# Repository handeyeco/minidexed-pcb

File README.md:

> [!CAUTION]
> This project was made by a JavaScript developer, not an electrical engineer.
>
> It should be assumed that everything is wrong and the project will set your house on fire.
>
> I am not responsible for anything ever.

# MiniDexed PCB

Custom PCB for [MiniDexed](https://github.com/probonopd/MiniDexed), an open-source FM synthesizer. It has:

- An endless encoder
- 3 Cherry buttons (back/home/select)
- A 1602 display
- 3.5mm TRS MIDI in/thru/out
- USB MIDI
- 3.5mm TRS audio out (via the PCM5102 DAC)

See the [writeup on my blog](https://handeyeco.github.io/tech-blog/minidexed-pcb/) for a full explanation of the circuit.

Thanks to lots of folks!

- [probonopd](https://github.com/probonopd) and the whole MiniDexed team
- [diyelectromusic](https://diyelectromusic.com/) for MiniDexed work and PCB design notes
- The whole [Dexed](https://github.com/asb2m10/dexed) lineage
- The [KiCad](https://www.kicad.org/) maintainers

## Builds

Look in `/gerbers/` for build files and BOMs.

### 20240727

Working with the [MiniDexed 2024-01-16 release](https://github.com/probonopd/MiniDexed/releases/tag/2024-01-16).

No known issues (although MIDI out is untested right now). The whole thing is about the size of a Korg NTS-1 and costs roughly $15/PCB to make (including SMT assembly and SMT parts; not including the Pi, THT components, or shipping).

Required changes to `minidexed.ini`:

```
# Sound device
SoundDevice=i2s
#SoundDevice=pwm
#SoundDevice=hdmi

# ...unchanged...

ButtonPinBack=16
ButtonActionBack=click
ButtonPinSelect=27
ButtonActionSelect=click
ButtonPinHome=26
ButtonActionHome=click

# ...unchanged...
```

- For JLCPCB PCB assembly
  - SMD BOM is `minidexed-bom-smd.csv`
  - Pick-and-place position file is `minidexed-bottom-pos.csv`
  - I'm not an expert and can't help much, I followed [this video](https://www.youtube.com/watch?v=VejO8rDdhzo)
- Non-SMD components:
  - x1 [RPi](https://www.adafruit.com/product/3055)
    - I used the 3 because the 4 is hot AF
  - x3 [Cherry switches](https://www.digikey.com/en/products/detail/cherry-americas-llc/MX1A-E1NW/20180) 
    - PCB-mount is best: `MX1A-_1NW`, the `W` is PCB mount
  - x3 Cherry compatible key caps
  - x1 Encoder
    - I have no idea what encoder I used, [maybe this](https://www.digikey.com/en/products/detail/bourns-inc/PEC11R-4215F-S0012/4499664?s=N4IgTCBcDaIGwFYwFoAKBRAwgRmwJWQBYxsEAxZAZWwgF0BfIA)
    - I used a switched encoder
    - Shaft height/style depends on the enclosure/knob
  - x1 Knob for the encoder
  - x4 3.5mm TRS
    - [Like this one](https://www.mouser.com/ProductDetail/SparkFun/PRT-08032?qs=WyAARYrbSnZFBWwuc8Qktw%3D%3D)
    - I like the switched ones because they have 5 pins vs 3 pins which makes the connection to the PCB more solid
    - MIDI is TRS, that's why there's 4 (x3 MIDI, x1 audio)
  - x1 16x2 LCD display
    - My understanding is that these 16x2 LCDs are pretty generic, something [like this](https://www.adafruit.com/product/181) should work
  - x1 10k (103) trim pot
    - For the LCD; [like these](https://www.amazon.com/gp/product/B0CZVY726N)
  - x1 2x20 2.54mm female header (for the Pi)
  - x1 1x16 2.54mm male header (for the LCD)
  - x1 1x16 2.54mm female header (for the LCD)
    - optional, I soldered mine into the PCB to keep things short
  - I think all the mounting holes and spacers are M2.5 (since that's what the Pi uses)
  - All this stuff is pretty generic and highly available
  - **Don't trust me**, double check your footprints or be prepared to reorder things

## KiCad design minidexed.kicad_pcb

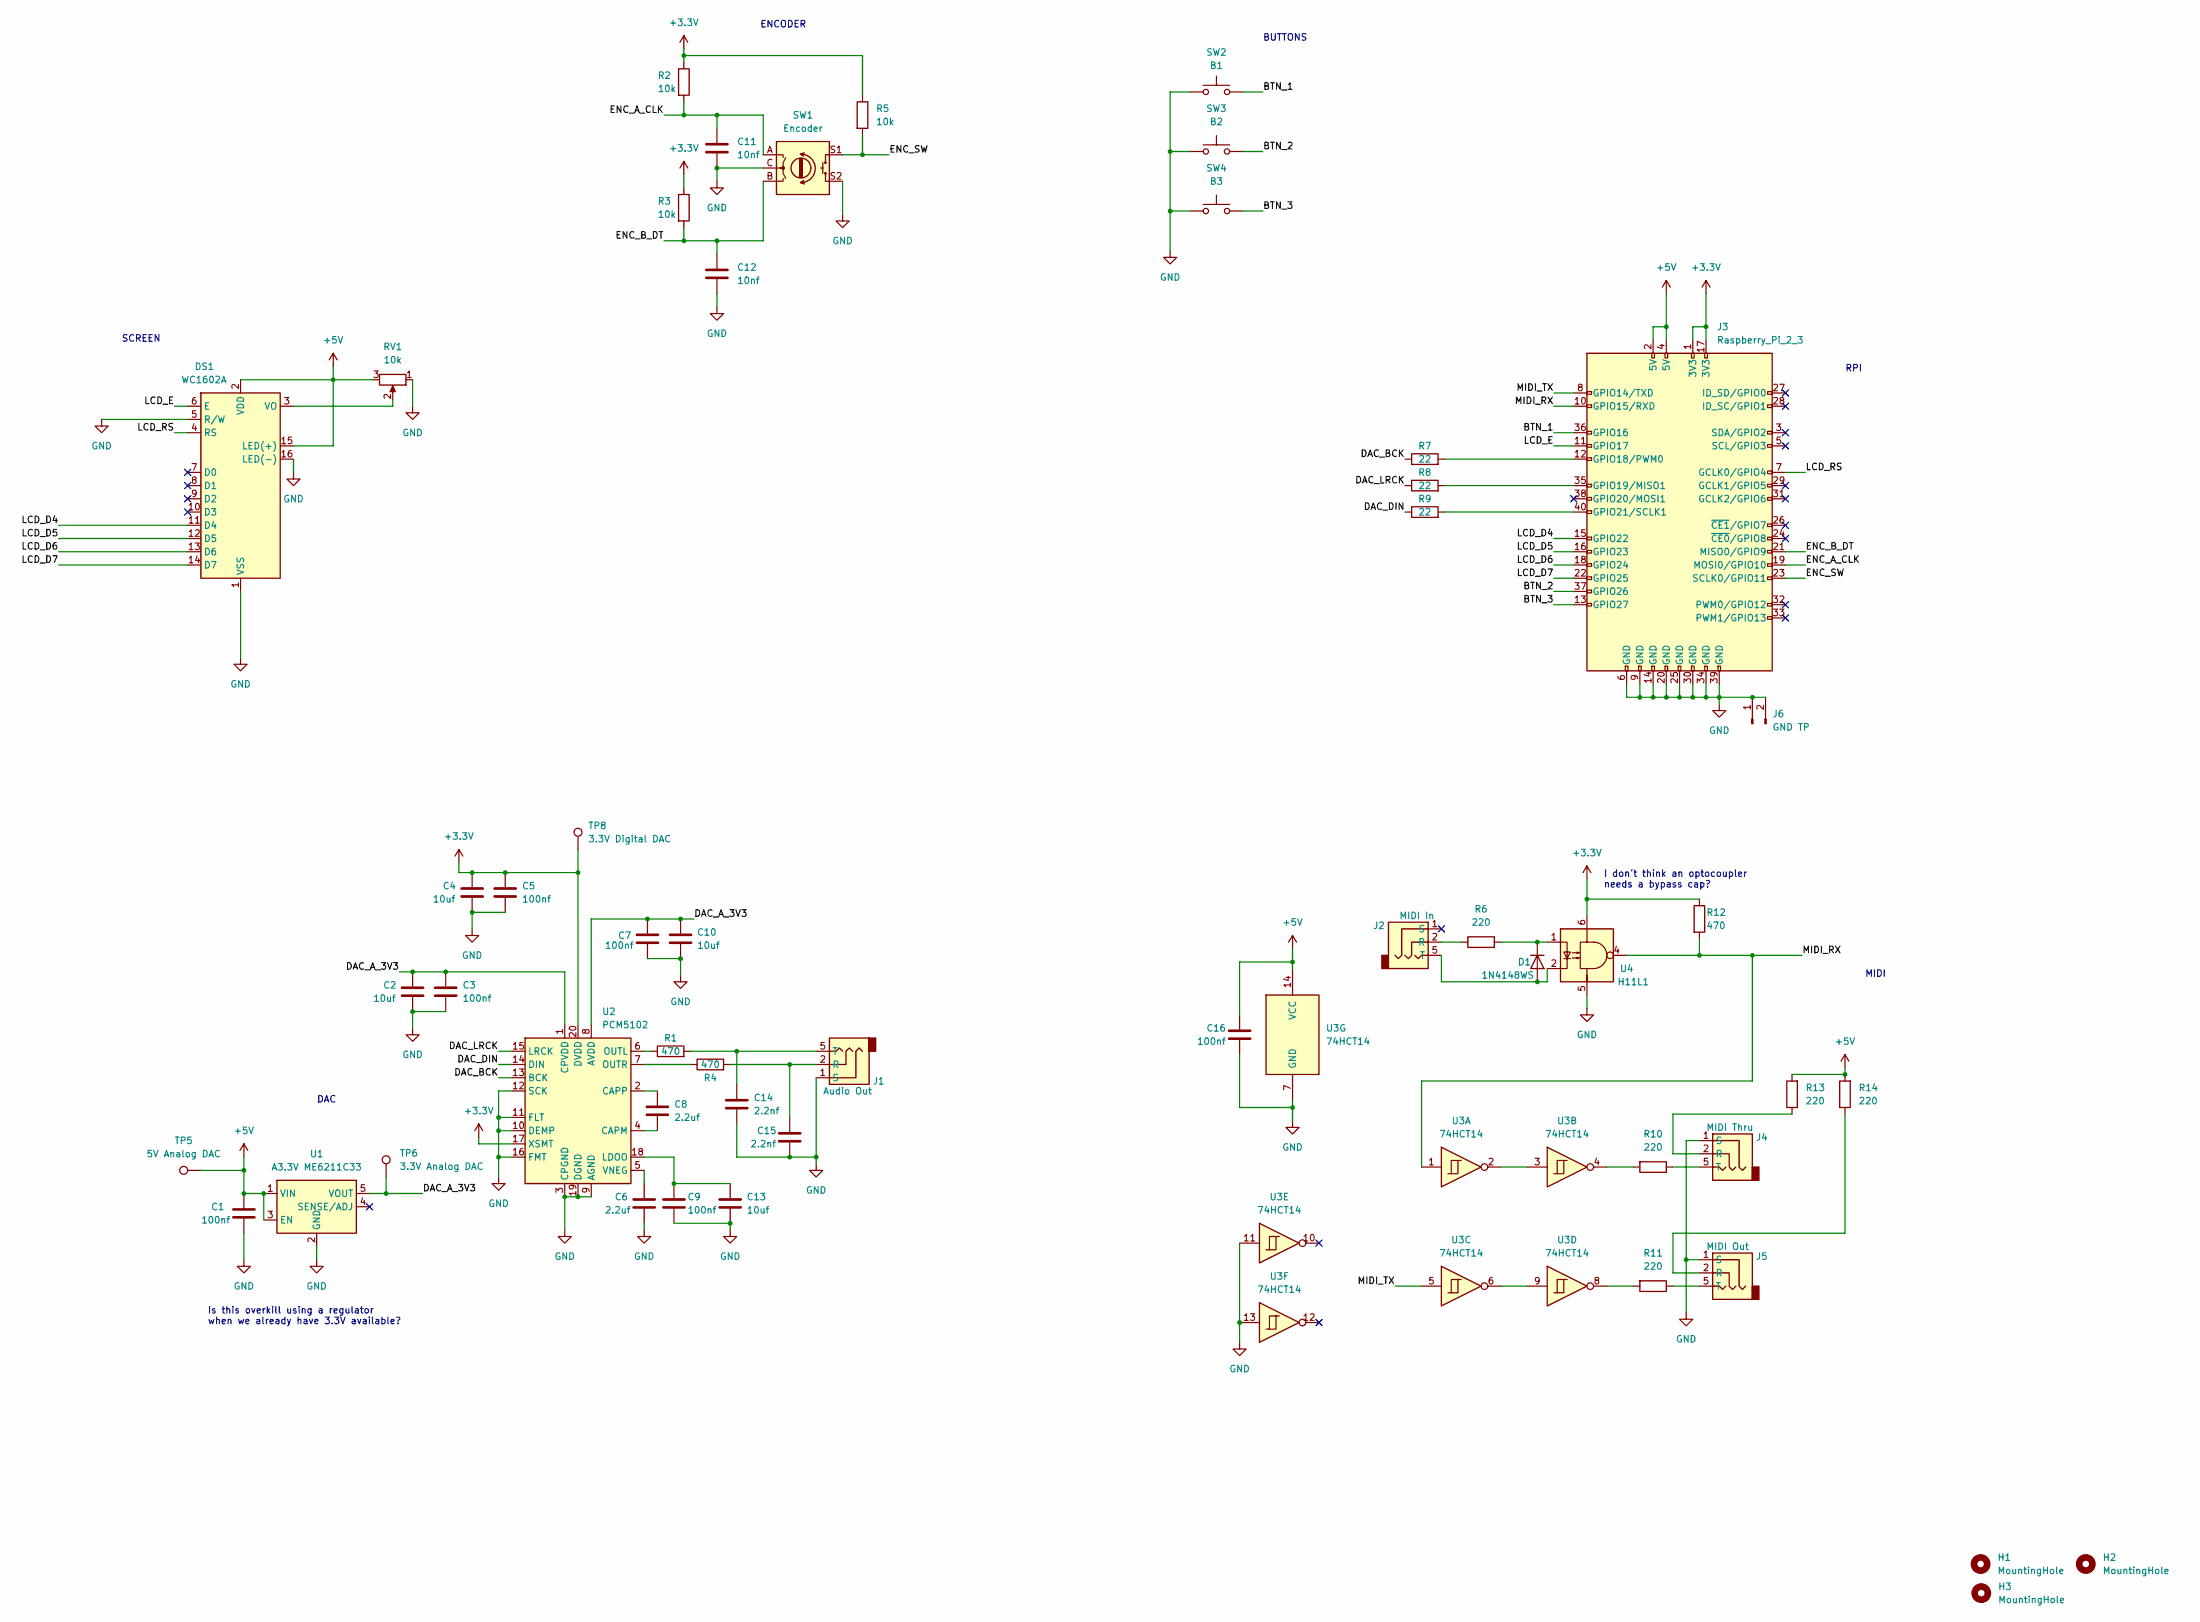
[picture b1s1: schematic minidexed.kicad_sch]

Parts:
C1, C3, C5, C7, C9, C16: 100nf; C_0805_2012Metric_Pad1.18x1.45mm_HandSolder; LCSC C472810
C2, C4, C10, C13: 10uf; C_0805_2012Metric_Pad1.18x1.45mm_HandSolder; LCSC C111662
C6, C8: 2.2uf; C_0805_2012Metric_Pad1.18x1.45mm_HandSolder; LCSC C6119894
C11, C12: 10nf; C_0805_2012Metric_Pad1.18x1.45mm_HandSolder; LCSC C77455
C14, C15: 2.2nf; C_0805_2012Metric_Pad1.18x1.45mm_HandSolder; LCSC C395967
D1: 1N4148WS; D_SOD-323; LCSC C2128
DS1: WC1602A
H1, H2, H3: MountingHole; MountingHole_2.7mm_M2.5
J1: Audio Out; sparkfun_3.5mm_trs
J2: MIDI In; sparkfun_3.5mm_trs
J3: Raspberry_Pi_2_3; raspberry-pi_rpi_hat
J4: MIDI Thru; sparkfun_3.5mm_trs
J5: MIDI Out; sparkfun_3.5mm_trs
J6: GND TP; PinHeader_1x02_P2.54mm_Vertical
R1, R4, R12: 470; R_1206_3216Metric_Pad1.30x1.75mm_HandSolder; LCSC C104814
R2, R3, R5: 10k; R_1206_3216Metric_Pad1.30x1.75mm_HandSolder; LCSC C2073539
R6, R10, R11, R13, R14: 220; R_1206_3216Metric_Pad1.30x1.75mm_HandSolder; LCSC C872616
R7, R8, R9: 22; R_1206_3216Metric_Pad1.30x1.75mm_HandSolder; LCSC C912903
RV1: 10k; Potentiometer_Runtron_RM-065_Vertical
SW1: Encoder; RotaryEncoder_Alps_EC11E-Switch_Vertical_H20mm
SW2: B1; SW_Cherry_MX_1.00u_PCB
SW3: B2; SW_Cherry_MX_1.00u_PCB
SW4: B3; SW_Cherry_MX_1.00u_PCB
TP5: 5V Analog DAC; TestPoint_Pad_D1.0mm
TP6: 3.3V Analog DAC; TestPoint_Pad_D1.0mm
TP8: 3.3V Digital DAC; TestPoint_Pad_D1.0mm
U1: A3.3V ME6211C33; TSOT-23-5; LCSC C82942
U2: PCM5102; TSSOP-20_4.4x6.5mm_P0.65mm; LCSC C107671
U3: 74HCT14; TSSOP-14_4.4x5mm_P0.65mm; LCSC C133639
U4: H11L1; SOP-6_6.5x7.12mm_P2.54mm; LCSC C78589

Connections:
+3.3V: C4.1, C5.1, J3.1 (3V3), J3.17 (3V3), R2.1, R3.1, R5.1, R12.1, TP8.1, U2.17 (XSMT), U2.20 (DVDD), U4.6
+5V: C1.1, C16.1, DS1.2 (VDD), DS1.15 (LED(+)), J3.2 (5V), J3.4 (5V), R13.2, R14.2, RV1.3, TP5.1, U1.1 (VIN), U1.3 (EN), U3.14 (VCC)
/BTN_1: J3.36 (GPIO16), SW2.2
/BTN_2: J3.37 (GPIO26), SW3.2
/BTN_3: J3.13 (GPIO27), SW4.2
/DAC_A_3V3: C2.1, C3.1, C7.1, C10.1, TP6.1, U1.5 (VOUT), U2.1 (CPVDD), U2.8 (AVDD)
/DAC_BCK: R7.1, U2.13 (BCK)
/DAC_DIN: R9.1, U2.14 (DIN)
/DAC_LRCK: R8.1, U2.15 (LRCK)
/ENC_A_CLK: C11.1, J3.19 (MOSI0/GPIO10), R2.2, SW1.A
/ENC_B_DT: C12.1, J3.21 (MISO0/GPIO9), R3.2, SW1.B
/ENC_SW: J3.23 (SCLK0/GPIO11), R5.2, SW1.S1
/LCD_D4: DS1.11 (D4), J3.15 (GPIO22)
/LCD_D5: DS1.12 (D5), J3.16 (GPIO23)
/LCD_D6: DS1.13 (D6), J3.18 (GPIO24)
/LCD_D7: DS1.14 (D7), J3.22 (GPIO25)
/LCD_E: DS1.6 (E), J3.11 (GPIO17)
/LCD_RS: DS1.4 (RS), J3.7 (GCLK0/GPIO4)
/MIDI_RX: J3.10 (GPIO15/RXD), R12.2, U3.1, U4.4
/MIDI_TX: J3.8 (GPIO14/TXD), U3.5
GND: C1.2, C2.2, C3.2, C4.2, C5.2, C6.2, C7.2, C9.2, C10.2, C11.2, C12.2, C13.2, C14.2, C15.2, C16.2, DS1.1 (VSS), DS1.5 (R/W), DS1.16 (LED(-)), J1.1 (S), J3.6 (GND), J3.9 (GND), J3.14 (GND), J3.20 (GND), J3.25 (GND), J3.30 (GND), J3.34 (GND), J3.39 (GND), J4.1 (S), J5.1 (S), J6.1, J6.2, RV1.1, SW1.C, SW1.S2, SW2.1, SW3.1, SW4.1, U1.2 (GND), U2.3 (CPGND), U2.9 (AGND), U2.10 (DEMP), U2.11 (FLT), U2.12 (SCK), U2.16 (FMT), U2.19 (DGND), U3.7 (GND), U3.11, U3.13, U4.5
unnamed: C6.1, U2.5 (VNEG)
unnamed: C8.1, U2.2 (CAPP)
unnamed: C8.2, U2.4 (CAPM)
unnamed: C9.1, C13.1, U2.18 (LDOO)
unnamed: C14.1, J1.5 (T), R1.2
unnamed: C15.1, J1.2 (R), R4.2
unnamed: D1.1 (K), R6.2, U4.1
unnamed: D1.2 (A), J2.5 (T), U4.2
unnamed: DS1.3 (VO), RV1.2
unnamed: J2.2 (R), R6.1
unnamed: J3.12 (GPIO18/PWM0), R7.2
unnamed: J3.35 (GPIO19/MISO1), R8.2
unnamed: J3.40 (GPIO21/SCLK1), R9.2
unnamed: J4.2 (R), R13.1
unnamed: J4.5 (T), R10.1
unnamed: J5.2 (R), R14.1
unnamed: J5.5 (T), R11.1
unnamed: R1.1, U2.6 (OUTL)
unnamed: R4.1, U2.7 (OUTR)
unnamed: R10.2, U3.4
unnamed: R11.2, U3.8
unnamed: U3.2, U3.3
unnamed: U3.6, U3.9

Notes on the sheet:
Is this overkill using a regulator when we already have 3.3V available?
I don't think an optocoupler needs a bypass cap?
ENCODER
SCREEN
MIDI
BUTTONS
DAC
RPI

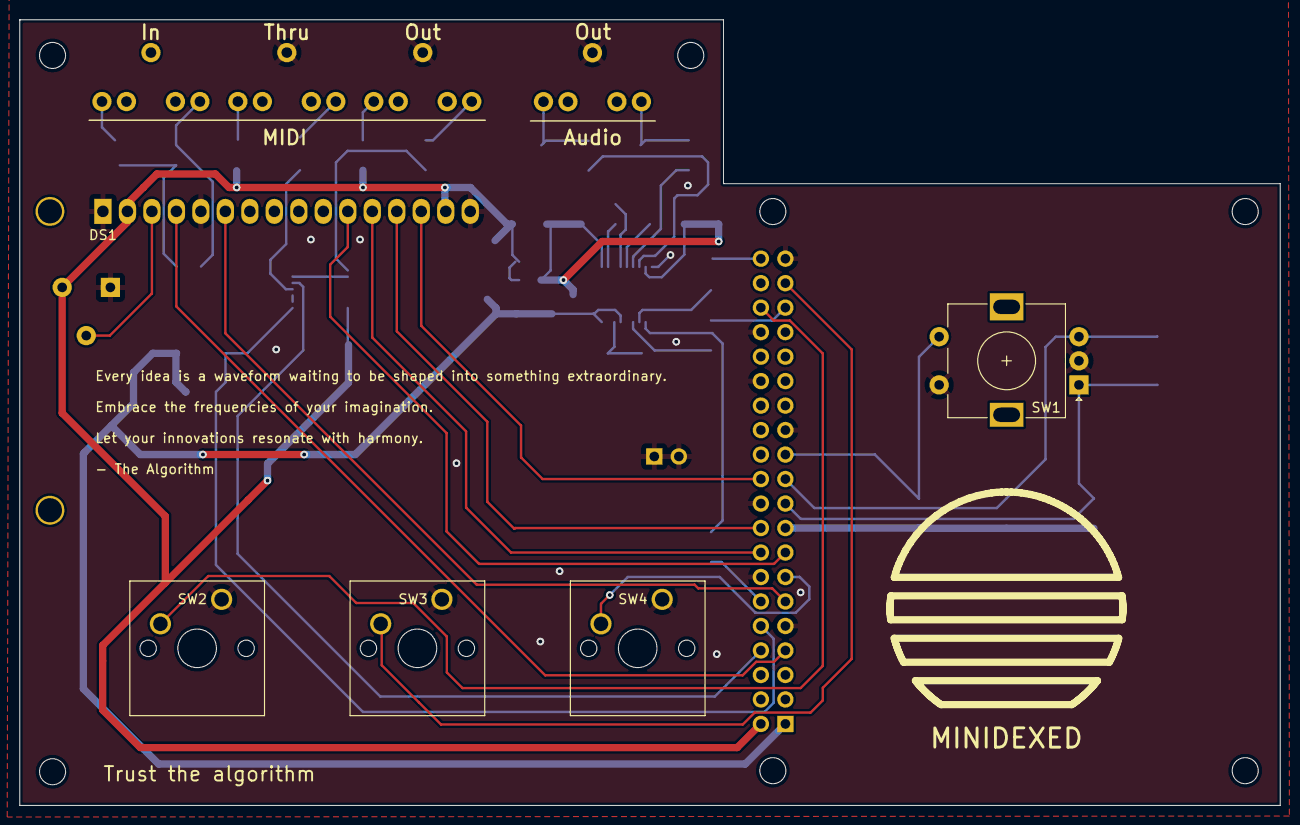
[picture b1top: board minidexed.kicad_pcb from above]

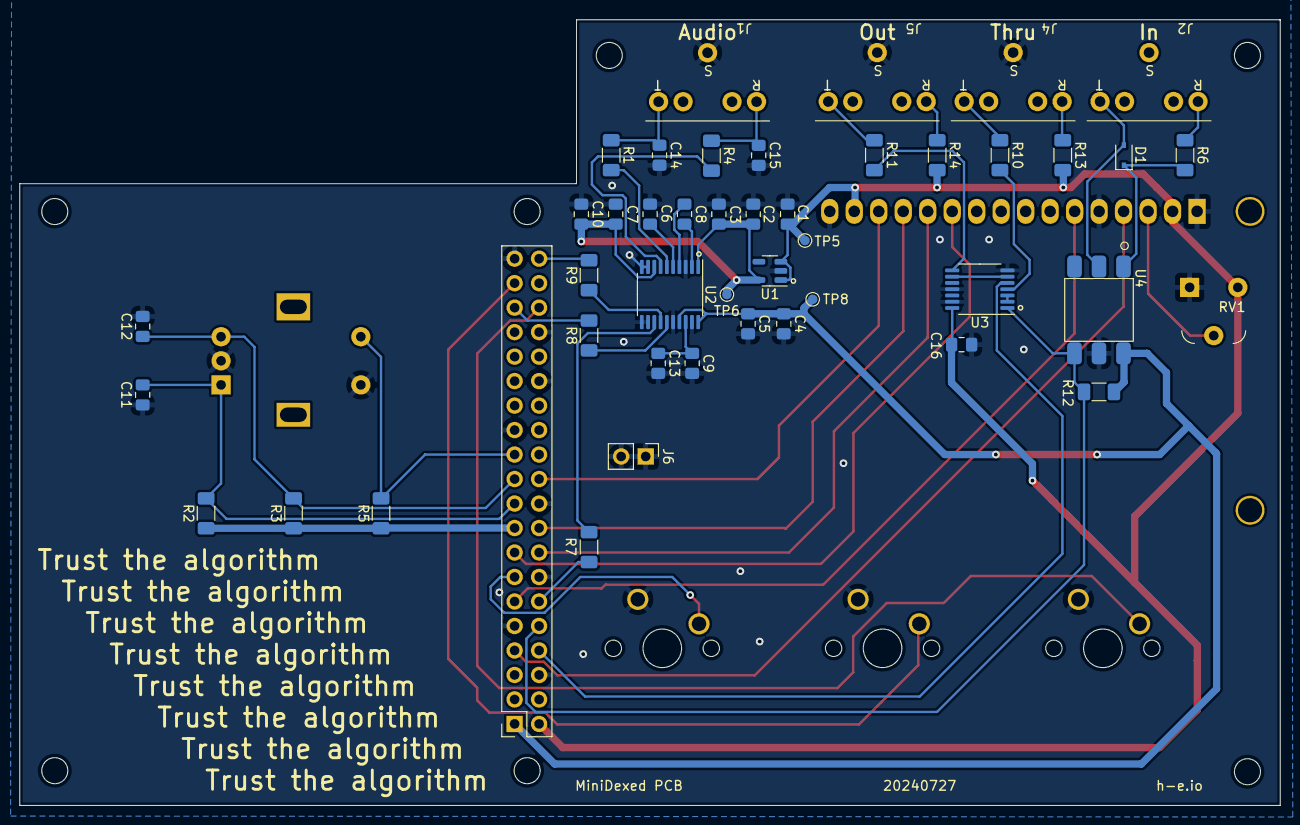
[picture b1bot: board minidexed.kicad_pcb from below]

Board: 2 copper layers, 130.8 x 81.5 mm, 53 parts (44 on the bottom side), 44 nets.

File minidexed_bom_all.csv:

Comment,Designator,Footprint,LCSC
"100nf","C1,C3,C5,C7,C9,C16","Capacitor_SMD:C_0805_2012Metric_Pad1.18x1.45mm_HandSolder","C472810"
"10nf","C11,C12","Capacitor_SMD:C_0805_2012Metric_Pad1.18x1.45mm_HandSolder","C77455"
"2.2nf","C14,C15","Capacitor_SMD:C_0805_2012Metric_Pad1.18x1.45mm_HandSolder","C395967"
"10uf","C2,C4,C10,C13","Capacitor_SMD:C_0805_2012Metric_Pad1.18x1.45mm_HandSolder","C111662"
"2.2uf","C6,C8","Capacitor_SMD:C_0805_2012Metric_Pad1.18x1.45mm_HandSolder","C6119894"
"1N4148WS","D1","Diode_SMD:D_SOD-323","C2128"
"WC1602A","DS1","Display:WC1602A",""
"MountingHole","H1,H2,H3","MountingHole:MountingHole_2.7mm_M2.5",""
"Audio Out","J1","sparkfun 3.5mm:sparkfun_3.5mm_trs",""
"MIDI In","J2","sparkfun 3.5mm:sparkfun_3.5mm_trs",""
"Raspberry_Pi_2_3","J3","raspberry-pi_rpi_hat:raspberry-pi_rpi_hat",""
"MIDI Thru","J4","sparkfun 3.5mm:sparkfun_3.5mm_trs",""
"MIDI Out","J5","sparkfun 3.5mm:sparkfun_3.5mm_trs",""
"GND TP","J6","Connector_PinHeader_2.54mm:PinHeader_1x02_P2.54mm_Vertical",""
"470","R1,R4,R12","Resistor_SMD:R_1206_3216Metric_Pad1.30x1.75mm_HandSolder","C104814"
"10k","R2,R3,R5","Resistor_SMD:R_1206_3216Metric_Pad1.30x1.75mm_HandSolder","C2073539"
"220","R6,R10,R11,R13,R14","Resistor_SMD:R_1206_3216Metric_Pad1.30x1.75mm_HandSolder","C872616"
"22","R7,R8,R9","Resistor_SMD:R_1206_3216Metric_Pad1.30x1.75mm_HandSolder","C912903"
"10k","RV1","Potentiometer_THT:Potentiometer_Runtron_RM-065_Vertical",""
"Encoder","SW1","Rotary_Encoder:RotaryEncoder_Alps_EC11E-Switch_Vertical_H20mm",""
"B1","SW2","Button_Switch_Keyboard:SW_Cherry_MX_1.00u_PCB",""
"B2","SW3","Button_Switch_Keyboard:SW_Cherry_MX_1.00u_PCB",""
"B3","SW4","Button_Switch_Keyboard:SW_Cherry_MX_1.00u_PCB",""
"5V Analog DAC","TP5","TestPoint:TestPoint_Pad_D1.0mm",""
"3.3V Analog DAC","TP6","TestPoint:TestPoint_Pad_D1.0mm",""
"3.3V Digital DAC","TP8","TestPoint:TestPoint_Pad_D1.0mm",""
"A3.3V ME6211C33","U1","Package_TO_SOT_SMD:TSOT-23-5","C82942"
"PCM5102","U2","Package_SO:TSSOP-20_4.4x6.5mm_P0.65mm","C107671"
"74HCT14","U3","Package_SO:TSSOP-14_4.4x5mm_P0.65mm","C133639"
"H11L1","U4","SOP-6_6.5x7.12mm_P2.54mm:SOP-6_6.5x7.12mm_P2.54mm","C78589"

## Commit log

2024-07-15 6N138 version
2024-07-20 pre-tracks
2024-07-21 rough out tracks
2024-07-21 .gitignore
2024-07-21 remove backups
2024-07-21 add image errors
2024-07-22 fix gnd issue
2024-07-22 fix missing GND connection
2024-07-22 rewire LED
2024-07-23 update opto footprint
2024-07-24 export files
2024-08-13 organize build files
2024-08-13 add readme
2024-08-13 tweak readme
2024-08-13 add image
2024-08-13 try again
2024-09-29 add acrylic faceplates
2024-11-07 add blog link to README
2024-12-13 add parts to README
